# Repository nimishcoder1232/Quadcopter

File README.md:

# DIY-Quad-Copter
I want to make a drone that is completely autonomous, with my own flight computer. I will not use any drone control software; rather, I will make it all. The code from scratch, to learn as much as I can.

For the outpost submission, I will request S teir, rather than A teir. My reasons are following:

1. Custom Flight Control Software

The drone's flight software is entirely custom and has been developed from scratch by me. Unlike drones that rely on commercial off-the-shelf (COTS) flight control software such as Betaflight or similar systems, this project requires the development of a complete flight control stack, including sensor fusion, state estimation, and stabilization algorithms.

Developing this software has required extensive research into control systems, quaternion-based orientation estimation, complementary filters, and drone dynamics. Additionally, I anticipate multiple iterations and redesigns of the software before achieving reliable flight performance, making this a highly ambitious component of the project.

2. GPS-Based Autonomous Navigation

This drone is designed to support GPS navigation capabilities. The current codebase already contains foundational GPS-related functionality, and future development will include point-to-point autonomous navigation.

Implementing autonomous navigation significantly increases the complexity of the system, as it requires integration of GPS data with the flight controller, position estimation, waypoint tracking, and autonomous control logic.

3. Custom Ground Control System

In the PCB folder, you can see that I designed my own drone control board, rather than a COTS solution. 

CAD Screenshot: 

PCB Schematic: 

PCB Routing:

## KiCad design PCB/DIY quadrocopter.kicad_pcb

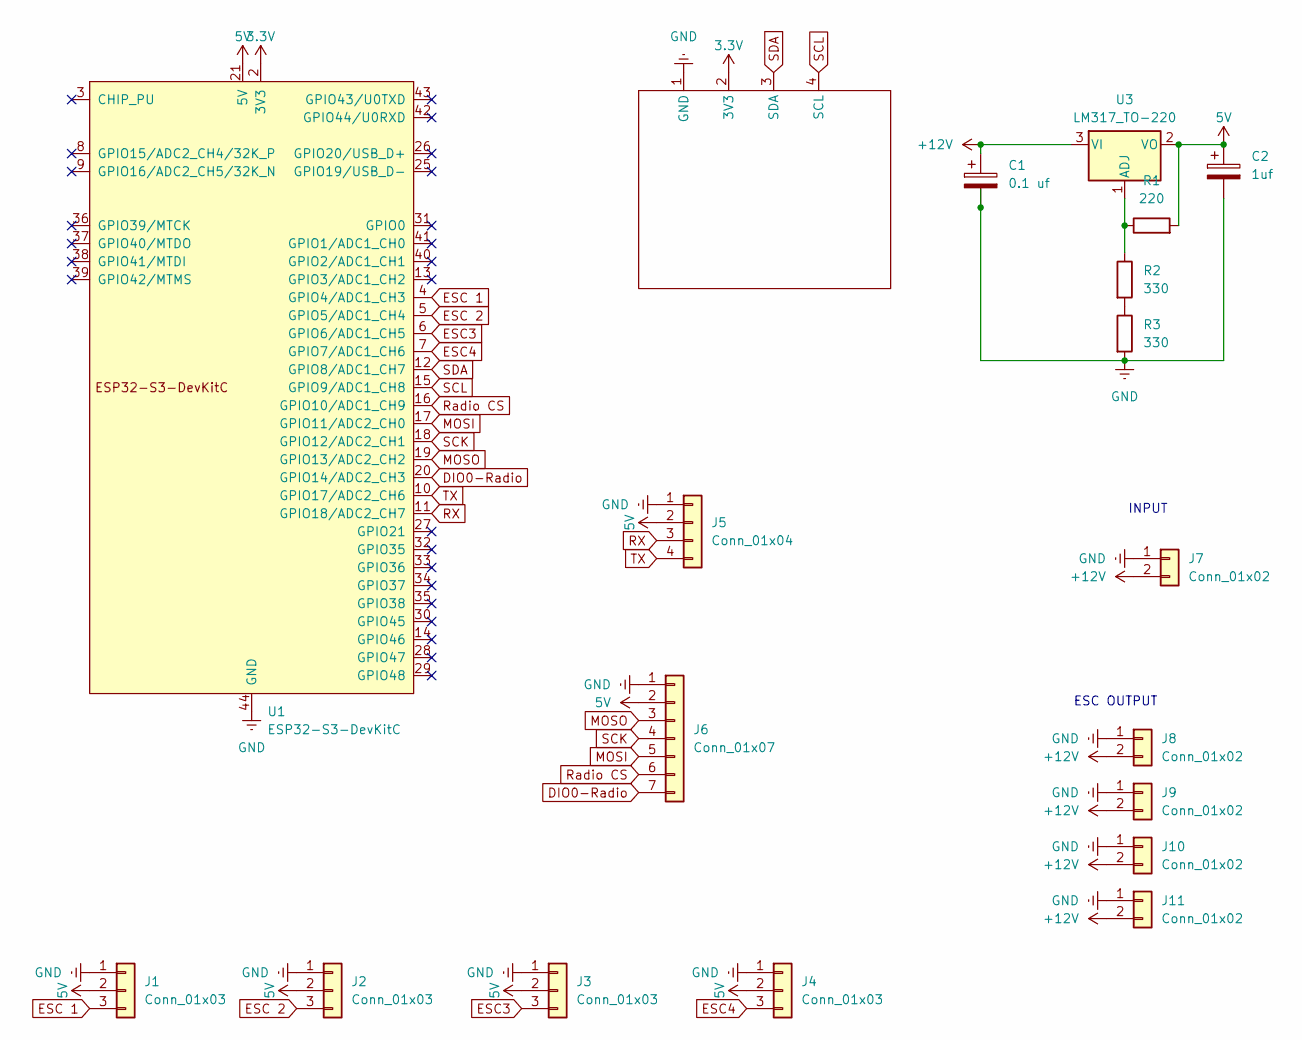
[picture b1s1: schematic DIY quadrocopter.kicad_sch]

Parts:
C1: 0.1 uf; CP_Radial_D5.0mm_P2.50mm
C2: 1uf; CP_Radial_D5.0mm_P2.50mm
J1, J2, J3, J4: Conn_01x03; PinHeader_1x03_P2.54mm_Vertical
J5: Conn_01x04; PinHeader_1x04_P2.54mm_Vertical
J6: Conn_01x07; PinHeader_1x07_P2.54mm_Vertical
J7, J8, J9, J10, J11: Conn_01x02; SolderWire-2sqmm_1x02_P7.8mm_D2mm_OD3.9mm
R1: 220; R_Axial_DIN0309_L9.0mm_D3.2mm_P12.70mm_Horizontal
R2, R3: 330; R_Axial_DIN0309_L9.0mm_D3.2mm_P12.70mm_Horizontal
U1: ESP32-S3-DevKitC; ESPP 32
U2: BMI270; PinHeader_1x06_P2.54mm_Vertical
U3: LM317_TO-220; TO-220-3_Vertical

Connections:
3.3V: U1.1 (3V3), U1.2 (3V3), U2.2 (3V3)
5V: C2.1, J1.2, J2.2, J3.2, J4.2, J5.2, J6.2, R1.2, U1.21 (5V), U3.2 (VO)
+12V: C1.1, J7.2, J8.2, J9.2, J10.2, J11.2, U3.3 (VI)
DIO0-Radio: J6.7, U1.20 (GPIO14/ADC2_CH3)
ESC3: J3.3, U1.6 (GPIO6/ADC1_CH5)
ESC4: J4.3, U1.7 (GPIO7/ADC1_CH6)
ESC 1: J1.3, U1.4 (GPIO4/ADC1_CH3)
ESC 2: J2.3, U1.5 (GPIO5/ADC1_CH4)
GND: C1.2, C2.2, J1.1, J2.1, J3.1, J4.1, J5.1, J6.1, J7.1, J8.1, J9.1, J10.1, J11.1, R3.2, U1.22 (GND), U1.23 (GND), U1.24 (GND), U1.44 (GND), U2.1 (GND)
MOSI: J6.5, U1.17 (GPIO11/ADC2_CH0)
MOSO: J6.3, U1.19 (GPIO13/ADC2_CH2)
unnamed: R2.2, R3.1
unnamed: R1.1, R2.1, U3.1 (ADJ)
RX: J5.3, U1.11 (GPIO18/ADC2_CH7)
Radio CS: J6.6, U1.16 (GPIO10/ADC1_CH9)
SCK: J6.4, U1.18 (GPIO12/ADC2_CH1)
SCL: U1.15 (GPIO9/ADC1_CH8), U2.4 (SCL)
SDA: U1.12 (GPIO8/ADC1_CH7), U2.3 (SDA)
TX: J5.4, U1.10 (GPIO17/ADC2_CH6)

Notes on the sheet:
INPUT
ESC OUTPUT

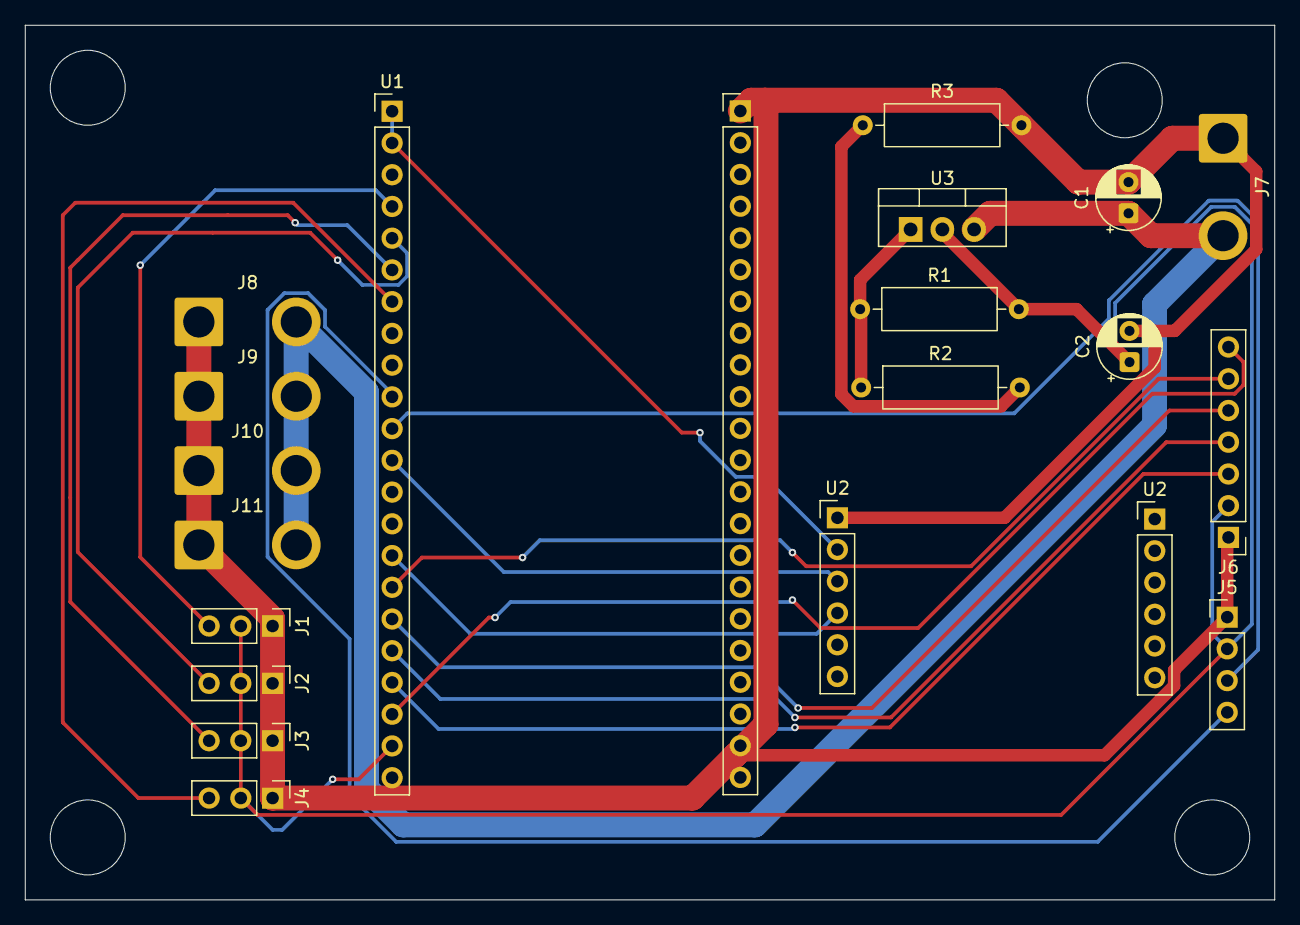
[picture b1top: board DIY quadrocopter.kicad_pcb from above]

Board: 2 copper layers, 100.0 x 70.0 mm, 20 parts (0 on the bottom side), 19 nets.

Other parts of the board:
U2#2: BMI270; PinHeader_1x06_P2.54mm_Vertical

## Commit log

2026-06-17 update file
2026-06-17 Rename dronefinalcad.step to CAD/dronefinalcad.step
2026-06-17 Rename DIY quadrocopter.kicad_pcb to PCB/DIY quadrocopter.kicad_pcb
2026-06-17 Rename DIY quadrocopter.kicad_prl to PCB/DIY quadrocopter.kicad_prl
2026-06-17 Rename DIY quadrocopter.kicad_pro to PCB/DIY quadrocopter.kicad_pro
2026-06-17 Rename DIY quadrocopter.kicad_sch to PCB/DIY quadrocopter.kicad_sch
2026-06-18 worked on code
2026-06-18 Rename Flightcode.c to CODE/ Flightcode.c
2026-06-18 Enhance README with project details and images
    Expanded the README to detail custom flight control software, GPS navigation, and ground control system.
2026-06-18 Rename Drone BOMB - Sheet1.csv to BOM.csv
2026-06-24 computersidecode
2026-06-25 worked on computer code
2026-06-25 added step
